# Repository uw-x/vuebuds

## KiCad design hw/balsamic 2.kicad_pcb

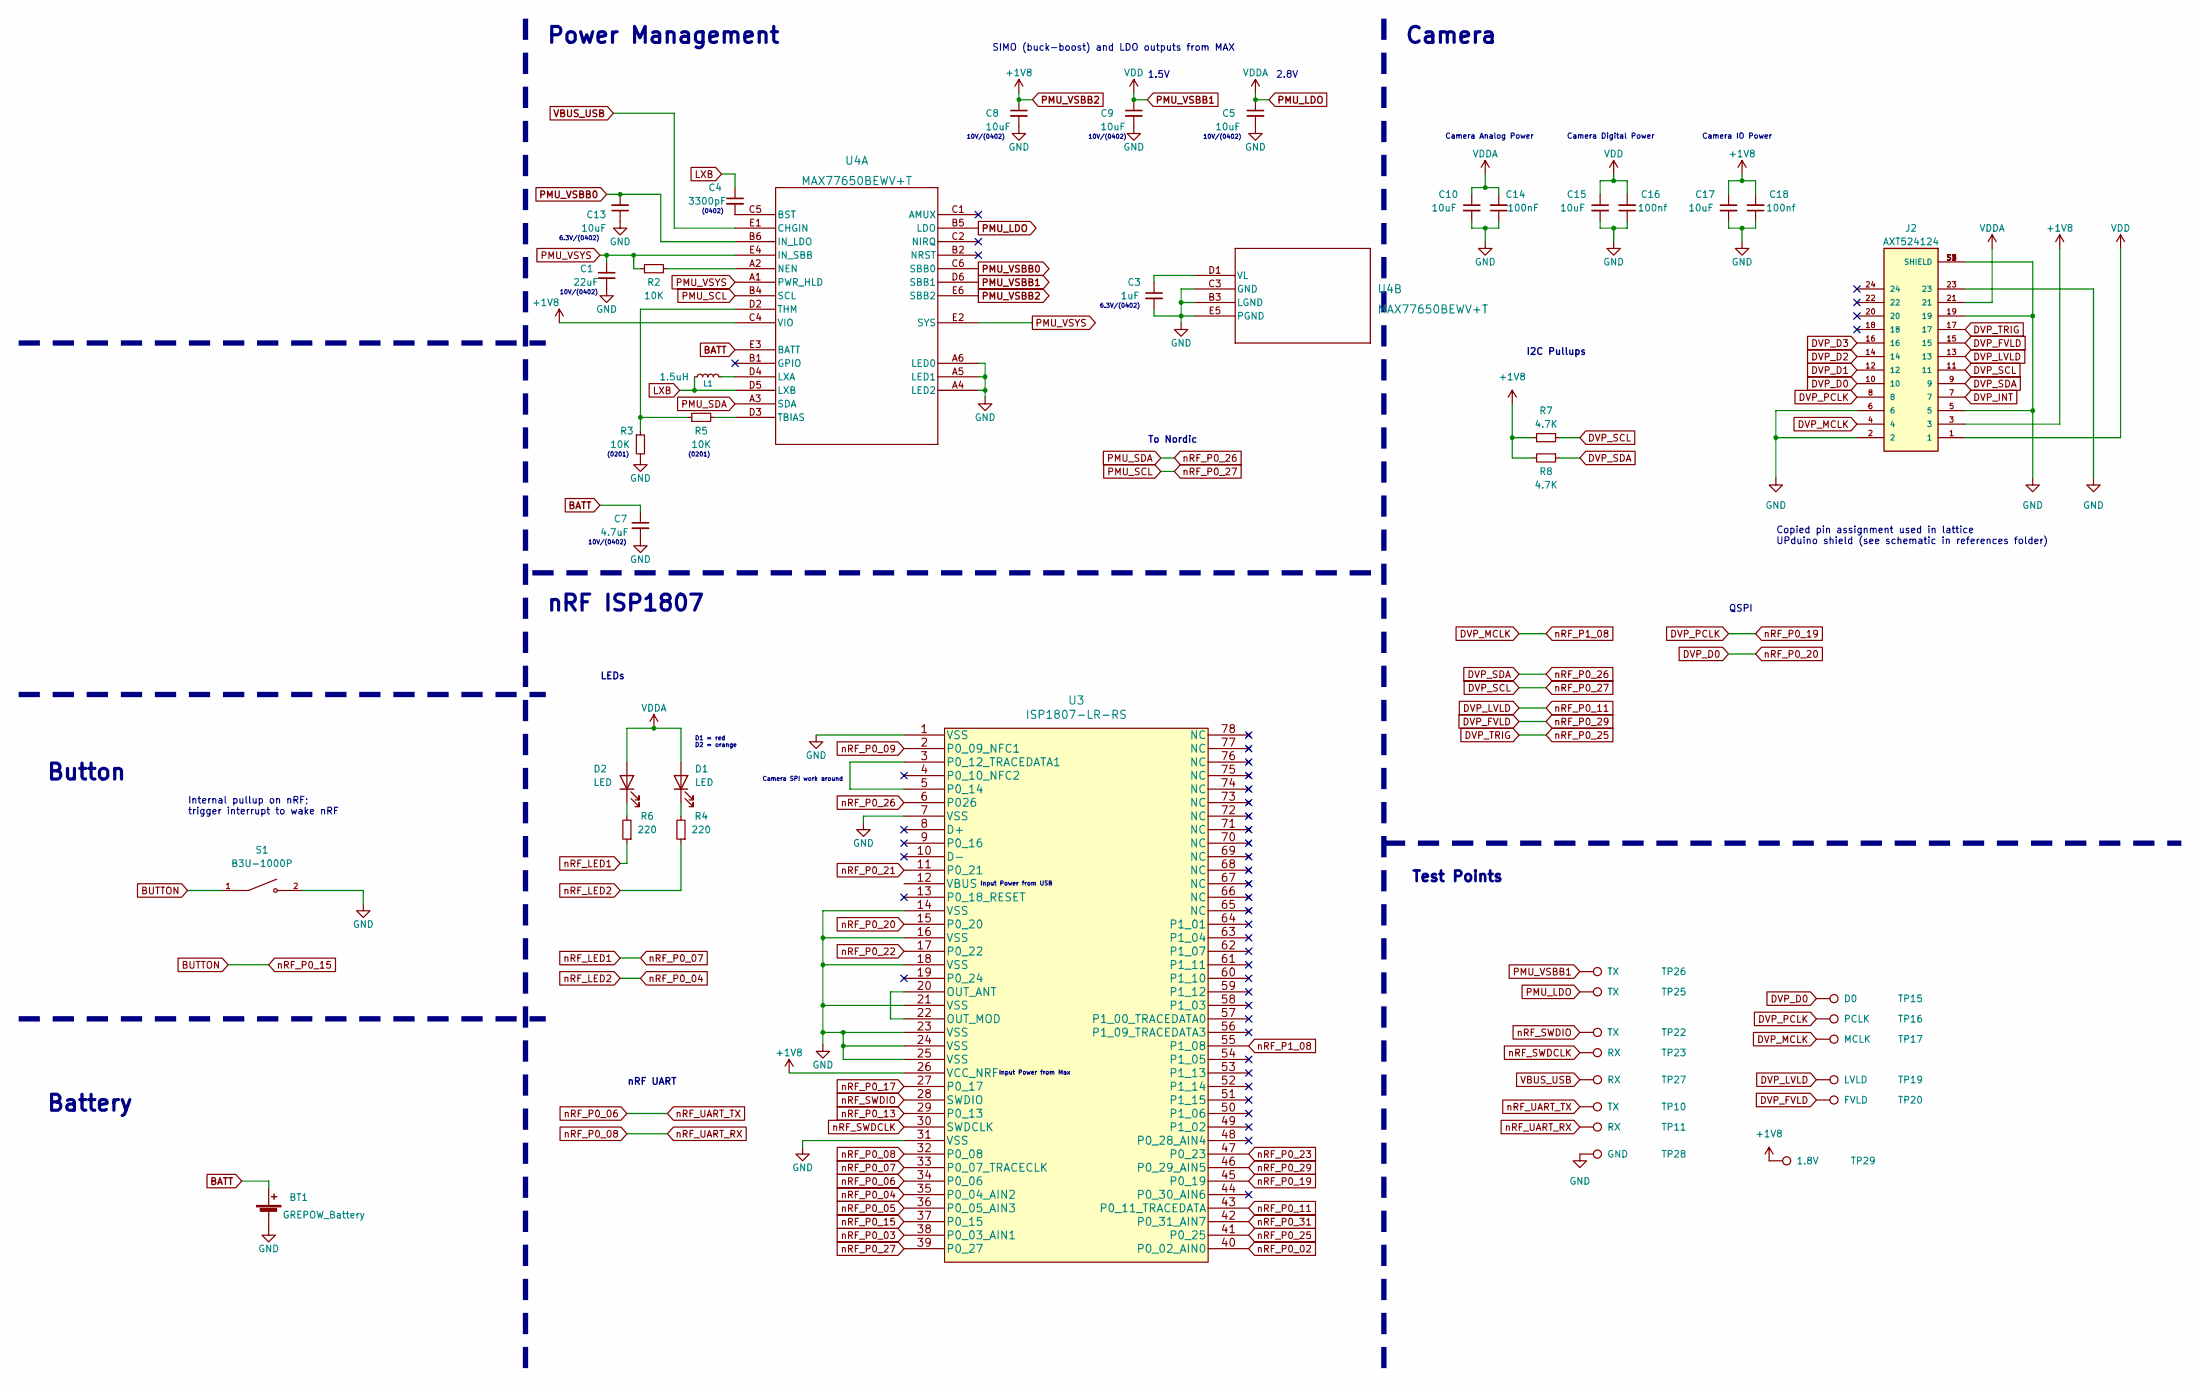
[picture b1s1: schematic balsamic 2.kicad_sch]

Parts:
BT1: GREPOW_Battery; balsamic_grepow_battery
C1: 22uF; C_0402_1005Metric
C3: 1uF; C_0402_1005Metric
C4: 3300pF; C_0402_1005Metric
C5, C8, C9, C13, C15, C17: 10uF; C_0402_1005Metric
C7: 4.7uF; C_0402_1005Metric
C10: 10uF; C_0402_1005Metric_Pad0.74x0.62mm_HandSolder
C14: 100nF; C_0201_0603Metric
C16, C18: 100nf; C_0201_0603Metric
D1, D2: LED; LED_0402_1005Metric
J2: AXT524124; PANASONIC_AXT524124
L1: 1.5uH; L_0805_2012Metric
R2, R3, R5: 10K; R_0201_0603Metric
R4, R6: 220; R_0201_0603Metric
R7, R8: 4.7K; R_0201_0603Metric
S1: B3U-1000P; SW_B3U-1000P
TP10, TP22, TP25, TP26: TX; TestPoint_Pad_D0.5mm
TP11, TP23, TP27: RX; TestPoint_Pad_D0.5mm
TP15: D0; TestPoint_Pad_D0.5mm
TP16: PCLK; TestPoint_Pad_D0.5mm
TP17: MCLK; TestPoint_Pad_D0.5mm
TP19: LVLD; TestPoint_Pad_D0.5mm
TP20: FVLD; TestPoint_Pad_D0.5mm
TP28: GND; TestPoint_Pad_D0.5mm
TP29: 1.8V; TestPoint_Pad_D0.5mm
U3: ISP1807-LR-RS
U4: MAX77650BEWV+T; 21-100047A_W302H2&plus_1_MXM

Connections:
BATT: BT1.1 (+), C7.1, U4.E3 (BATT)
BUTTON: S1.1, U3.37 (P0_15)
DVP_D0: J2.10, TP15.1, U3.15 (P0_20)
DVP_D1: J2.12
DVP_D2: J2.14
DVP_D3: J2.16
DVP_FVLD: J2.15, TP20.1, U3.46 (P0_29_AIN5)
DVP_INT: J2.7
DVP_LVLD: J2.13, TP19.1, U3.43 (P0_11_TRACEDATA)
DVP_MCLK: J2.4, TP17.1, U3.55 (P1_08)
DVP_PCLK: J2.8, TP16.1, U3.45 (P0_19)
DVP_SCL: J2.11, R7.2, U3.39 (P0_27), U4.B4 (SCL)
DVP_SDA: J2.9, R8.1, U3.6 (P026), U4.A3 (SDA)
DVP_TRIG: J2.17, U3.41 (P0_25)
GND: BT1.2 (-), C1.2, C3.2, C5.2, C7.2, C8.2, C9.2, C10.2, C13.1, C14.1, C15.2, C16.1, C17.2, C18.1, J2.2, J2.5, J2.6, J2.19, J2.23, J2.S1 (SHIELD), J2.S2 (SHIELD), J2.S3 (SHIELD), J2.S4 (SHIELD), R3.2, S1.2, TP28.1, U3.1 (VSS), U3.7 (VSS), U3.14 (VSS), U3.16 (VSS), U3.18 (VSS), U3.21 (VSS), U3.23 (VSS), U3.24 (VSS), U3.25 (VSS), U3.31 (VSS), U4.A4 (LED2), U4.A5 (LED1), U4.A6 (LED0), U4.B3 (LGND), U4.C3 (GND), U4.E5 (PGND)
LXB: C4.1, L1.1, U4.D5 (LXB)
unnamed: D1.1 (K), R4.2
unnamed: D2.1 (K), R6.2
unnamed: U3.20 (OUT_ANT), U3.22 (OUT_MOD)
unnamed: U3.3 (P0_12_TRACEDATA1), U3.5 (P0_14)
unnamed: C4.2, U4.C5 (BST)
unnamed: L1.2, U4.D4 (LXA)
unnamed: R2.2, U4.A2 (NEN)
unnamed: R5.2, U4.D3 (TBIAS)
unnamed: R3.1, R5.1, U4.D2 (THM)
unnamed: C3.1, U4.D1 (VL)
PMU_LDO: C5.1, C10.1, C14.2, D1.2 (A), D2.2 (A), J2.21, TP25.1, U4.B5 (LDO)
PMU_VSBB0: C13.2, U4.B6 (IN_LDO), U4.C6 (SBB0)
PMU_VSBB1: C9.1, C15.1, C16.2, J2.1, TP26.1, U4.D6 (SBB1)
PMU_VSBB2: C8.1, C17.1, C18.2, J2.3, R7.1, R8.2, TP29.1, U3.26 (VCC_NRF), U4.C4 (VIO), U4.E6 (SBB2)
PMU_VSYS: C1.1, R2.1, U4.A1 (PWR_HLD), U4.E2 (SYS), U4.E4 (IN_SBB)
VBUS_USB: TP27.1, U4.E1 (CHGIN)
nRF_LED1: R6.1, U3.33 (P0_07_TRACECLK)
nRF_LED2: R4.1, U3.35 (P0_04_AIN2)
nRF_P0_02: U3.40 (P0_02_AIN0)
nRF_P0_03: U3.38 (P0_03_AIN1)
nRF_P0_05: U3.36 (P0_05_AIN3)
nRF_P0_06: TP10.1, U3.34 (P0_06)
nRF_P0_08: TP11.1, U3.32 (P0_08)
nRF_P0_09: U3.2 (P0_09_NFC1)
nRF_P0_13: U3.29 (P0_13)
nRF_P0_17: U3.27 (P0_17)
nRF_P0_21: U3.11 (P0_21)
nRF_P0_22: U3.17 (P0_22)
nRF_P0_23: U3.47 (P0_23)
nRF_P0_31: U3.42 (P0_31_AIN7)
nRF_SWDCLK: TP23.1, U3.30 (SWDCLK)
nRF_SWDIO: TP22.1, U3.28 (SWDIO)

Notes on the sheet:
2.8V
Battery
Button
10V/(0402)
D1 = red D2 = orange
1.5V
Camera IO Power
Input Power from USB
Input Power from Max
Test Points
6.3V/(0402)
Camera SPI work around
(0402)
To Nordic
Camera Digital Power
(0201)
nRF ISP1807
Internal pullup on nRF; trigger interrupt to wake nRF
SIMO (buck-boost) and LDO outputs from MAX
Copied pin assignment used in lattice UPduino shield (see schematic in references folder)
Camera Analog Power
LEDs
nRF UART
QSPI
Camera
I2C Pullups
Power Management

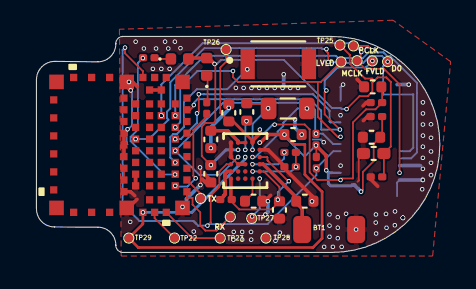
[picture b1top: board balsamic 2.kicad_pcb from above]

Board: 4 copper layers, 22.4 x 12.0 mm, 43 parts (1 on the bottom side), 34 nets.

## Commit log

2026-05-11 Open source fw/hw for vuebuds

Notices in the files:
parts and their libraries:
Copyright 2021 Accelerated Designs. All rights reserved.
